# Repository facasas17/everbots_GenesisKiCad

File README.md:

# everbots_GenesisKiCad
Esquematico placa de conexión Genesis

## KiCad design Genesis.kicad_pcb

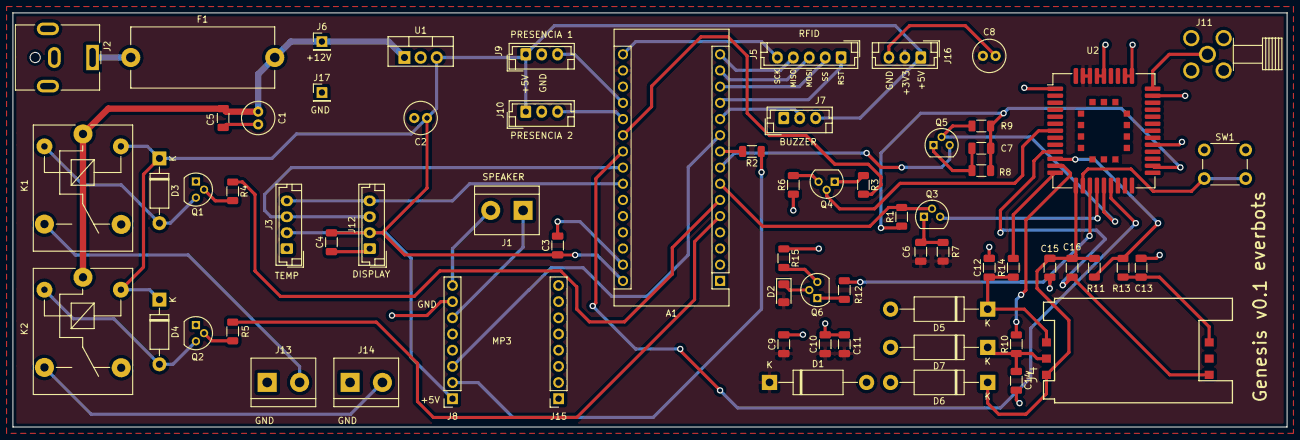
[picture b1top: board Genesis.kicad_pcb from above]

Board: 2 copper layers, 200.0 x 65.0 mm, 68 parts (0 on the bottom side), 54 nets.

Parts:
A1: Arduino_Nano
C1: 10u; C_Radial_D5.0mm_H11.0mm_P2.00mm
C2: 1u; C_Radial_D5.0mm_H11.0mm_P2.00mm
C3, C4, C9, C16: 100n; C_1206_3216Metric
C5: 220n; C_1206_3216Metric
C6, C7: 1n; C_1206_3216Metric
C8: 100u; C_Radial_D5.0mm_H11.0mm_P2.00mm
C10: 100p; C_1206_3216Metric
C11: 22p; C_1206_3216Metric
C12, C13, C14, C15: 33p; C_1206_3216Metric
D1, D5, D6, D7: P6KE12A; D_DO-15_P15.24mm_Horizontal
D2: LED_RED; LED_1206_3216Metric
D3, D4: 1N4007; D_DO-41_SOD81_P10.16mm_Horizontal
F1: Fuse; Fuseholder_Cylinder-5x20mm_Stelvio-Kontek_PTF78_Horizontal_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
J1, J13, J14: Conn_01x02; TerminalBlock_bornier-2_P5.08mm
J2: Jack-DC; BarrelJack_CUI_PJ-063AH_Horizontal
J3, J12: Conn_01x04; JST_EH_B4B-EH-A_1x04_P2.50mm_Vertical
J4: SIM; GCT_SIM5060-6-0-26-00-X_REVC
J5: Conn_01x05; JST_EH_B5B-EH-A_1x05_P2.50mm_Vertical
J6, J17: Conn_01x01; PinHeader_1x01_P2.54mm_Vertical
J7, J9, J10, J16: Conn_01x03; JST_EH_B3B-EH-A_1x03_P2.50mm_Vertical
J8, J15: Conn_01x08; PinSocket_1x08_P2.54mm_Vertical
J11: SMA; TE_221790-1
K1, K2: SANYOU_SRD_Form_C; Relay_SPDT_SANYOU_SRD_Series_Form_C
Q1, Q2: BC547; TO-92
Q3, Q4, Q5, Q6: BC546; TO-92
R1, R9, R11: 10k; R_1206_3216Metric
R2, R4, R5: 1k; R_1206_3216Metric
R3, R7, R8, R12: 4.7k; R_1206_3216Metric
R6, R15: 47k; R_1206_3216Metric
R10, R13, R14: 22; R_1206_3216Metric
SW1: SW_Push; SW_PUSH_6mm_H5mm
U1: LM7805_TO220; TO-220-3_Vertical
U2: BC66; Quectel_BC66

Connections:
+3V3: A1.17, C6.2, C8.1, C9.1, C10.1, C11.1, D1.1, D2.2, J16.2, R7.1, U2.42, U2.43
+5V: A1.30, C2.1, C3.1, C4.2, D3.1, D4.1, J3.2, J7.3, J8.1, J9.1, J10.1, J12.2, J16.1, K1.5, K2.5, U1.3
+12V: C1.1, C5.1, F1.2, J6.1, K1.1, K2.1, U1.1
/Bornera_grande: A1.6, R4.1
/Buzzer: A1.11, J7.2
/Cooler: A1.5, R5.1
/MISO: A1.15, J5.4
/MOSI: A1.14, J5.3
/PSM_EINT: A1.22, U2.19
/PWR_KEY: A1.21, R3.2
/Quectel_BC66/VDD_EXT: C7.2, R1.1, R8.1, R9.1, U2.24
/RST: A1.12, J5.1
/RXD_GSM: A1.7, Q3.2, R1.2
/RX_MP3: A1.9, R2.2
/SCK: A1.16, J5.5
/SCL: A1.24, J3.4, J12.4
/SDA: A1.23, J3.3, J12.3
/SS: A1.13, J5.2
/Sensor_presencia1: A1.20, J10.3
/Sensor_presencia2: A1.19, J9.3
/TXD_GSM: A1.8, Q5.3
/TX_MP3: A1.10, J8.3
GND: A1.4, A1.29, C1.2, C2.2, C3.2, C4.1, C5.2, C8.2, C9.2, C10.2, C11.2, C12.2, C13.2, C14.2, C15.2, D1.2, D5.2, D6.2, D7.2, J2.2, J3.1, J7.1, J8.7, J9.2, J10.2, J11.2, J11.3, J11.4, J11.5, J12.1, J13.1, J14.1, J16.3, J17.1, Q1.1, Q2.1, R6.1, R15.1, SW1.1, U1.2, U2.1, U2.27, U2.34, U2.36, U2.37, U2.40, U2.41
unnamed: C6.1, Q3.1, R7.2
unnamed: C7.1, Q5.1, R8.2
unnamed: C12.1, D5.1, J4.C3, R14.1
unnamed: C13.1, J4.C7, R13.1
unnamed: C14.1, D7.1, J4.C2, R10.1
unnamed: C15.1, C16.1, D6.1, J4.C1, R11.2, U2.14
unnamed: C16.2, J4.C5, U2.10
unnamed: D2.1, Q6.2
unnamed: D3.2, K1.2, Q1.3
unnamed: D4.2, K2.2, Q2.3
unnamed: F1.1, J2.1
unnamed: J1.1, J8.6
unnamed: J1.2, J8.8
unnamed: J8.2, R2.1
unnamed: J11.1, U2.35
unnamed: J13.2, K1.3
unnamed: J14.2, K2.3
unnamed: Q1.2, R4.2
unnamed: Q2.2, R5.2
unnamed: Q3.3, U2.17
unnamed: Q4.1, R3.1
unnamed: Q4.2, U2.7
unnamed: Q4.3, R6.2
unnamed: Q5.2, R9.2, U2.18
unnamed: Q6.1, R12.1
unnamed: Q6.3, R15.2
unnamed: R10.2, U2.12
unnamed: R11.1, R13.2, U2.11
unnamed: R12.2, U2.16
unnamed: R14.2, U2.13
unnamed: SW1.2, U2.15

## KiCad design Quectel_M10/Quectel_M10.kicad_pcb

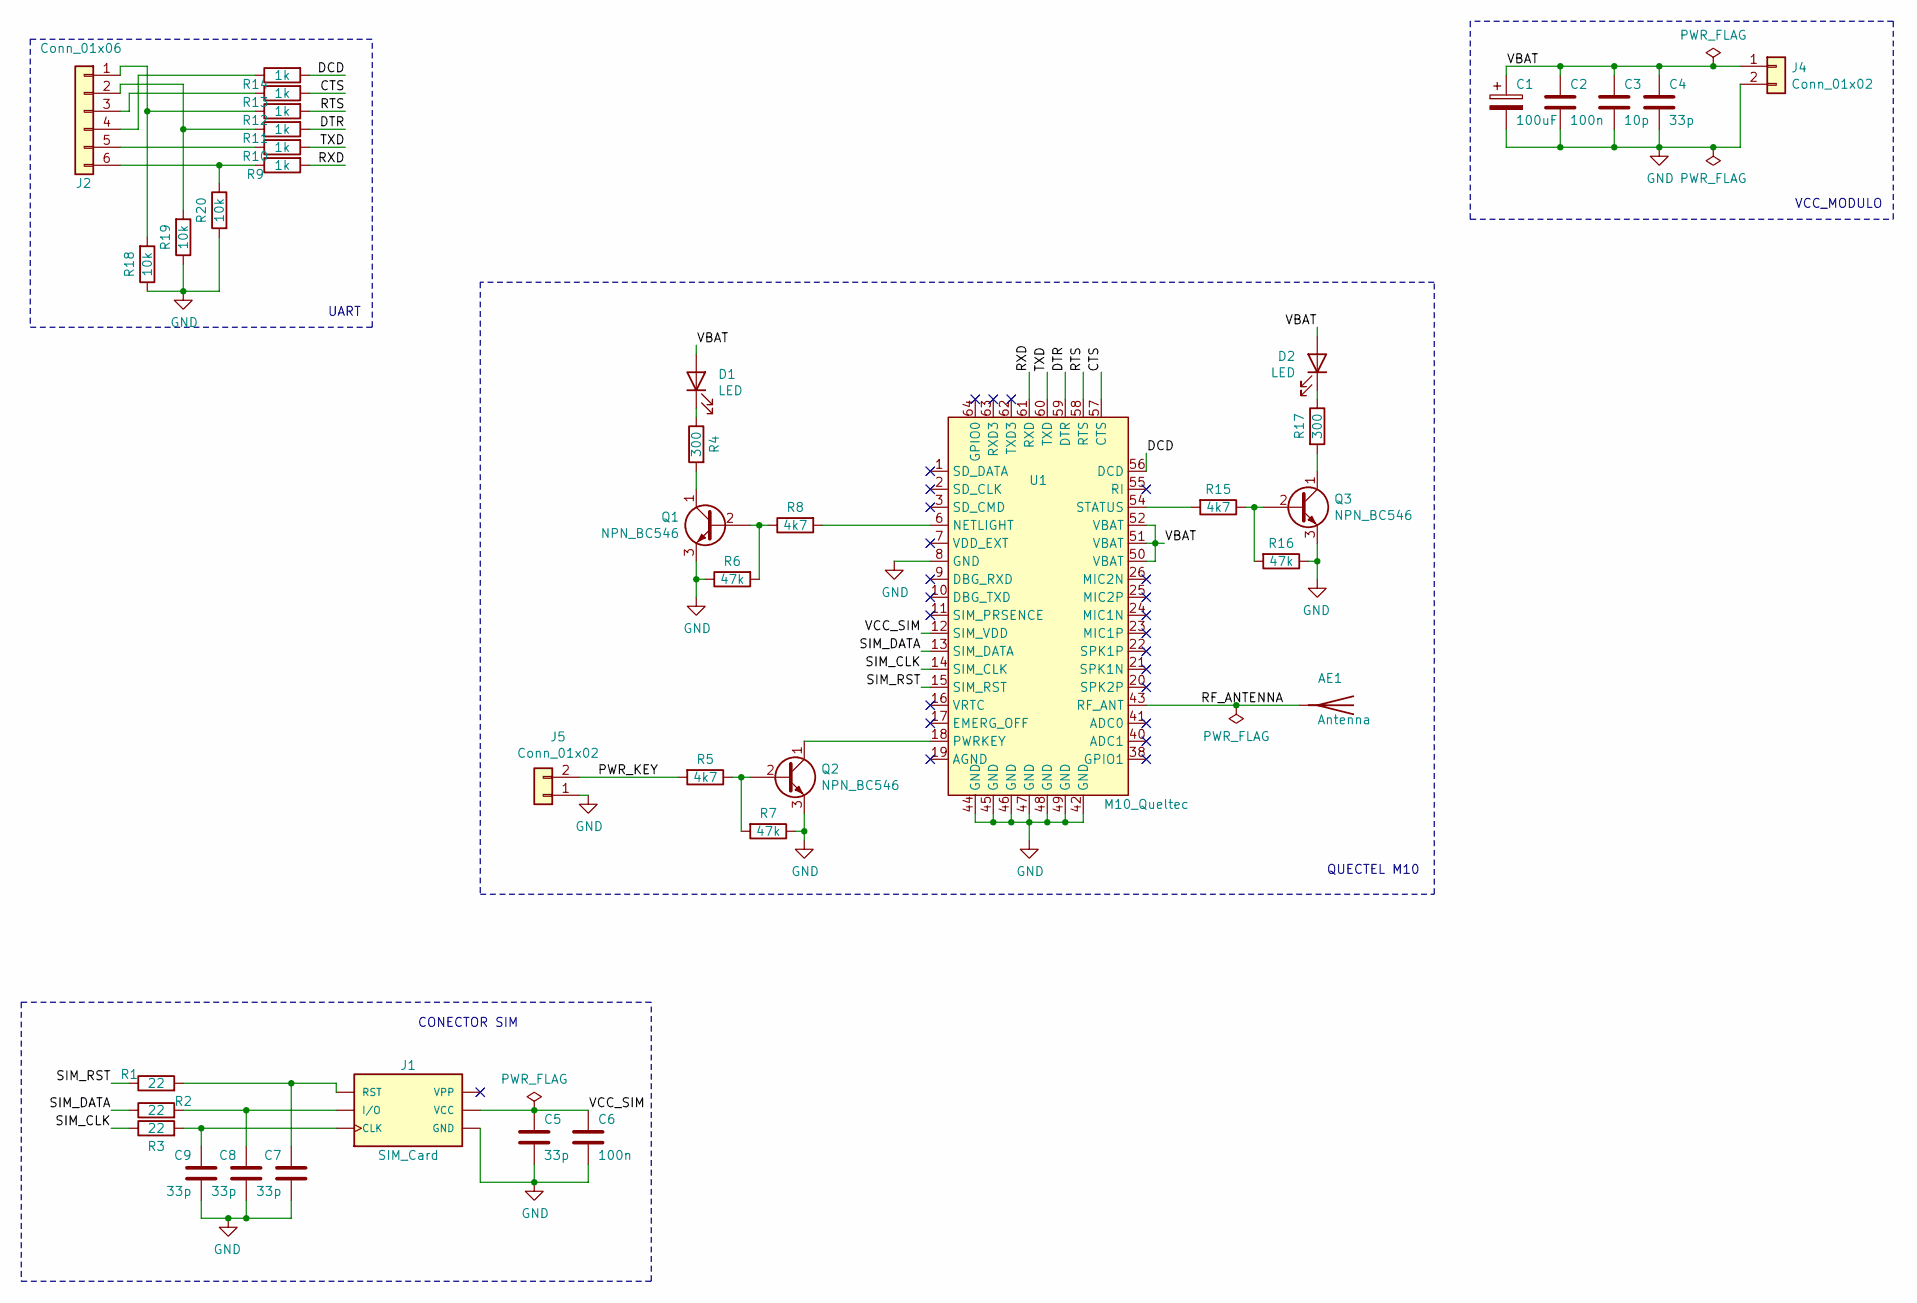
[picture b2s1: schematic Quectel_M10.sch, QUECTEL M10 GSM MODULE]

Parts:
AE1: Antenna; PinSocket_1x01_P2.54mm_Vertical
C1: 100uF; CP_Radial_Tantal_D7.0mm_P2.50mm
C2, C6: 100n; C_Disc_D6.0mm_W2.5mm_P5.00mm
C3: 10p; C_Disc_D6.0mm_W2.5mm_P5.00mm
C4, C5, C7, C8, C9: 33p; C_Disc_D6.0mm_W2.5mm_P5.00mm
D1, D2: LED; LED_D3.0mm
J1: SIM_Card; SIM_connector
J2: Conn_01x06; PinSocket_1x06_P2.54mm_Vertical
J4, J5: Conn_01x02; PinSocket_1x02_P2.54mm_Vertical
Q1, Q2, Q3: NPN_BC546; TO-92
R1, R2, R3: 22; R_Axial_DIN0207_L6.3mm_D2.5mm_P7.62mm_Horizontal
R4, R17: 300; R_Axial_DIN0207_L6.3mm_D2.5mm_P7.62mm_Horizontal
R5, R8, R15: 4k7; R_Axial_DIN0207_L6.3mm_D2.5mm_P7.62mm_Horizontal
R6, R7, R16: 47k; R_Axial_DIN0207_L6.3mm_D2.5mm_P7.62mm_Horizontal
R9, R10, R11, R12, R13, R14: 1k; R_Axial_DIN0207_L6.3mm_D2.5mm_P7.62mm_Horizontal
R18, R19, R20: 10k; R_Axial_DIN0207_L6.3mm_D2.5mm_P7.62mm_Horizontal
U1: M10_Queltec; PLCC-84_THT-Socket

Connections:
/CTS: R13.2, U1.57 (CTS)
/DCD: R14.2, U1.56 (DCD)
/DTR: R11.2, U1.59 (DTR)
/PWR_KEY: J5.2, R5.2
/RF_ANTENNA: AE1.1, U1.43 (RF_ANT)
/RTS: R12.2, U1.58 (RTS)
/RXD: R9.2, U1.61 (RXD)
/SIM_CLK: R3.1, U1.14 (SIM_CLK)
/SIM_DATA: R2.1, U1.13 (SIM_DATA)
/SIM_RST: R1.1, U1.15 (SIM_RST)
/TXD: R10.2, U1.60 (TXD)
/VBAT: C1.1, C2.1, C3.1, C4.1, D1.2 (A), D2.2 (A), J4.1, U1.50 (VBAT), U1.51 (VBAT), U1.52 (VBAT)
/VCC_SIM: C5.1, C6.1, J1.C1 (VCC), U1.12 (SIM_VDD)
GND: C1.2, C2.2, C3.2, C4.2, C5.2, C6.2, C7.2, C8.2, C9.2, J1.C5 (GND), J4.2, J5.1, Q1.3 (E), Q2.3 (E), Q3.3 (E), R6.1, R7.1, R16.1, R18.1, R19.1, R20.2, U1.8 (GND), U1.42 (GND), U1.44 (GND), U1.45 (GND), U1.46 (GND), U1.47 (GND), U1.48 (GND), U1.49 (GND)
unnamed: C7.1, J1.C2 (RST), R1.2
unnamed: C8.1, J1.C7 (I/O), R2.2
unnamed: C9.1, J1.C3 (CLK), R3.2
unnamed: D1.1 (K), R4.1
unnamed: D2.1 (K), R17.1
unnamed: J2.1, R12.1, R18.2
unnamed: J2.2, R11.1, R19.2
unnamed: J2.3, R13.1
unnamed: J2.4, R14.1
unnamed: J2.5, R10.1
unnamed: J2.6, R9.1, R20.1
unnamed: Q1.1 (C), R4.2
unnamed: Q1.2 (B), R6.2, R8.1
unnamed: Q2.1 (C), U1.18 (PWRKEY)
unnamed: Q2.2 (B), R5.1, R7.2
unnamed: Q3.1 (C), R17.2
unnamed: Q3.2 (B), R15.1, R16.2
unnamed: R8.2, U1.6 (NETLIGHT)
unnamed: R15.2, U1.54 (STATUS)
unnamed: U1.4 (RESERVED), U1.5 (RESERVED), U1.27 (RESERVED), U1.29 (RESERVED), U1.31 (RESERVED), U1.33 (RESERVED), U1.35 (RESERVED), U1.37 (RESERVED)
unnamed: U1.28 (RESERVED), U1.30 (RESERVED), U1.32 (RESERVED), U1.34 (RESERVED)
unnamed: U1.39 (RESERVED), U1.53 (RESERVED)

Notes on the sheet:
UART
CONECTOR SIM
VCC_MODULO
QUECTEL M10

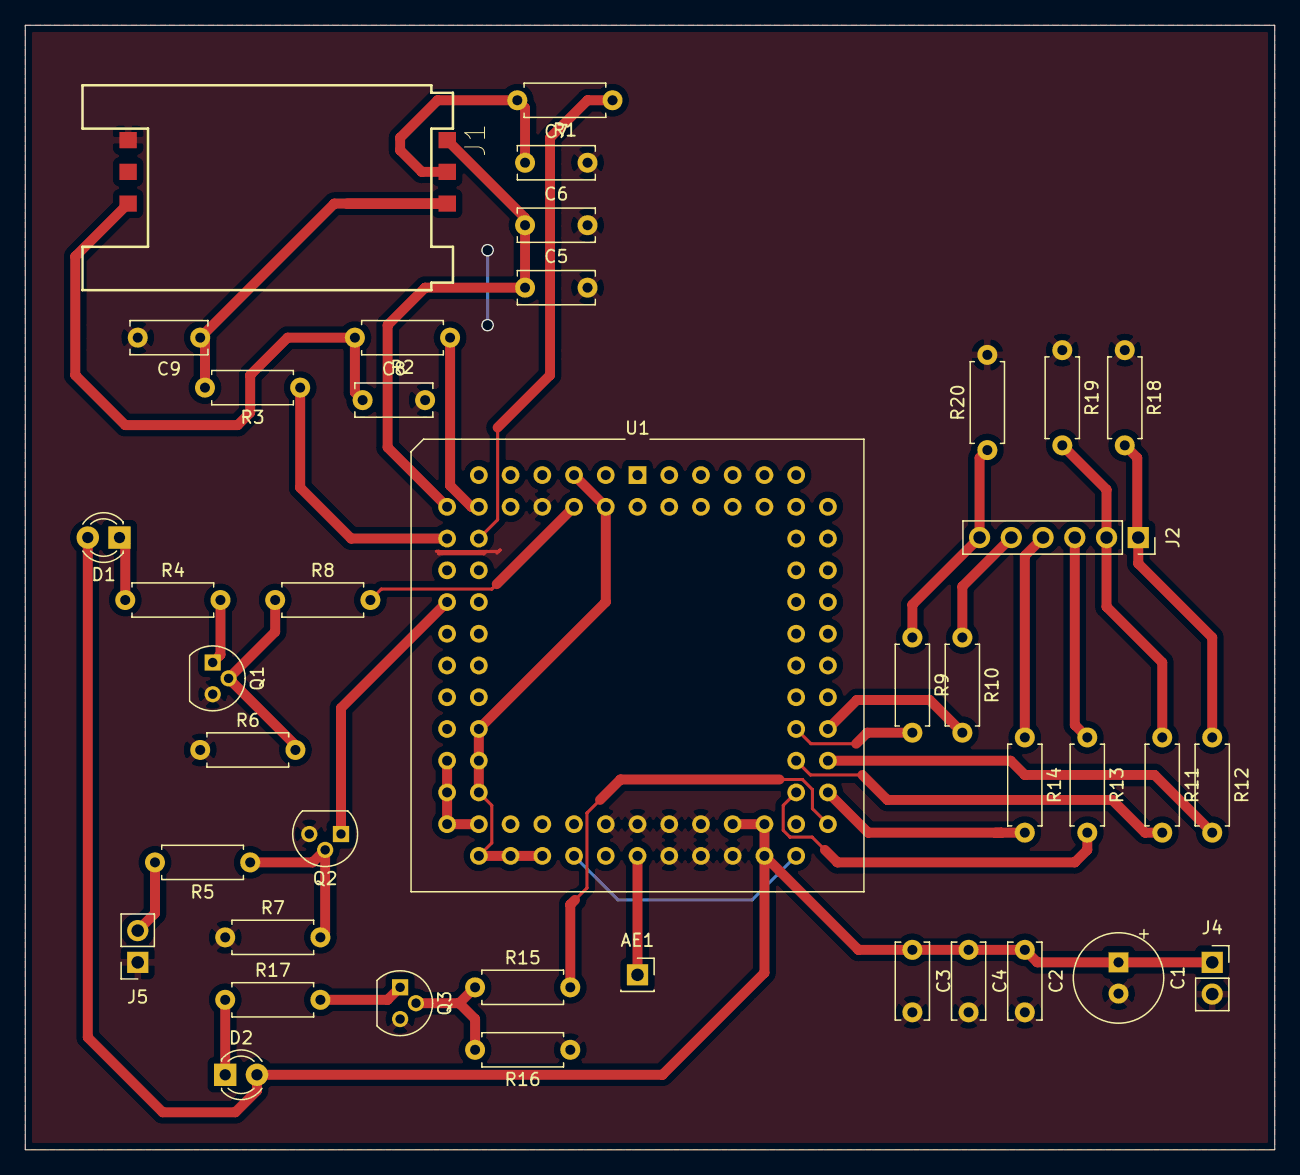
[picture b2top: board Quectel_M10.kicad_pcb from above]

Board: 2 copper layers, 100.0 x 90.0 mm, 40 parts (0 on the bottom side), 36 nets.

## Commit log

2021-02-10 Version 1.0 del esquematico de genesis
2021-02-11 Corrijo error de MP3
2021-05-22 Agrego modulo conector de chip GSM Quectel M10
2021-06-22 Incluyo BC66 en la misma placa
